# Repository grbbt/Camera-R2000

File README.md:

# R2000

> A compact, round-bodied digital camera built around the ESP32-P4, designed for fun, accessible photography with a deliberate film-inspired aesthetic.

---

## Overview

The R2000 is a hand-held digital camera on an 70mm circular PCB. Fixed-focus wide-angle lens, film-style filters, RGB flash, and a round touchscreen — all driven by an ESP32-P4 + ESP32-C6 SOM. It's a camera that prioritises feel and fun over clinical image quality.

---

## Features

- **80mm round PCB** — compact, pocketable form factor
- **OV5640 MIPI CSI-2 sensor** — 5MP, fixed focus, wide angle (~1.5m hyperfocal)
- **2.1" round ST7701S touchscreen** — live viewfinder and menu UI via LVGL
- **3-channel RGB flash** — independent R/G/B control for software-adjustable colour temperature
- **Film aesthetic filters** — colour grading, grain, vignette, and light leak applied in-camera
- **microSD card storage** — JPEG capture written directly from hardware encoder
- **USB-C** — charging and file transfer
- **1000mAh LiPo** — onboard single-cell battery

---

## Electrical Hardware

### Core SOM

**Guition JC-ESP32P4-M3-C6** — a dual-chip SOM combining:
- **ESP32-P4** — main application processor, MIPI CSI camera input, RGB display output, hardware JPEG encode, SD/MMC
- **ESP32-C6** — WiFi 6 / BLE 5 radio for wireless transfer and future remote control

### Schematic

### PCB

| Parameter | Value |
|-----------|-------|
| Diameter | 70mm |
| Layers | 4 |
| Design tool | KiCad |

- LDO bank placed adjacent to OV5640 to keep power traces short
- MT3608 boost converter isolated from camera rails to reduce switching noise
- RGB panel interface traces serpentined for length matching
- SD card traces kept short with 10kΩ pull-ups on CMD and DAT lines

### Camera

| Parameter | Value |
|-----------|-------|
| Sensor | OV5640 |
| Interface | MIPI CSI-2 (2-lane) |
| Resolution | 5MP (2592×1944) |
| Focus | Fixed, wide angle |
| Hyperfocal | ~1.5m (everything from ~80cm to ∞ sharp) |
| Autofocus | None — VCM unused |

### Display

| Parameter | Value |
|-----------|-------|
| Driver IC | ST7701S |
| Size | 2.1" round |
| Diameter | ~54mm |
| Interface | RGB parallel |
| Touch IC | GT911 (I2C) |

### Flash

Three independent channels let you tune the colour temperature of each shot in software — or go full auto white-balance assist by sampling the scene before firing.

| Channel | Driver | Supply |
|---------|--------|--------|
| Red 1W LED | AMC7135 (350mA CC) | 5V (MT3608 boost) |
| Green 1W LED | AMC7135 (350mA CC) | 5V (MT3608 boost) |
| Blue 1W LED | AMC7135 (350mA CC) | 5V (MT3608 boost) |

### Power

| Rail | Regulator | Supplies |
|------|-----------|---------|
| 3.3V | XC6210B332 (1A) | SOM, display logic, SD, GT911 |
| 2.8V | ME6211C28 (600mA) | OV5640 AVDD |
| 1.8V | ME6211C18 (600mA) | OV5640 DOVDD |
| 1.5V | ME6211C15 (600mA) | OV5640 DVDD |
| 5V (flash) | MT3608 boost | RGB flash rail |

Battery: 1000mAh single-cell LiPo, ~503040 form factor, charged via TP5100.

---

## Firmware

### Stack

| Layer | Component |
|-------|-----------|
| RTOS | FreeRTOS (via ESP-IDF v5.3+) |
| Camera | `esp_cam_sensor` + `esp_video` (MIPI CSI DMA) |
| JPEG encode | `esp_jpeg` — hardware-accelerated on ESP32-P4 |
| Display | `esp_lcd` (ST7701S) + `esp_lcd_touch` (GT911) |
| UI | LVGL — hardware-accelerated via P4 PPA |
| Storage | `esp_vfs_fat` + `sdmmc` |

### Task Architecture

```
Core 0                         Core 1
├── Camera capture task        ├── LVGL UI task
├── JPEG encode task           └── Touch polling task
└── SD write task
```

Both cores run in genuine parallel — the live viewfinder never stutters during a write.

### Capture Pipeline

```
OV5640 sensor
  └── MIPI CSI-2 DMA → PSRAM framebuffer
        └── HW JPEG encoder
              └── SD write (FAT32)
                    └── JPEG file
```

### Filters

- **Colour grading** — warm/cool/cross-process presets
- **Grain simulation** — luminance-dependent noise overlay
- **Vignette** — radial falloff, adjustable intensity
- **Light leak** — randomised edge flare, optional per-shot

---

## Getting Started

### Prerequisites

- ESP-IDF v5.3 or later ([installation guide](https://docs.espressif.com/projects/esp-idf/en/latest/esp32p4/get-started/))
- KiCad 8.x for hardware files

### Build Firmware

```bash
git clone https://github.com/yourusername/R2000.git
cd R2000/firmware

idf.py set-target esp32p4
idf.py menuconfig     # Set SD card GPIO, display config, etc.
idf.py build
idf.py -p /dev/ttyUSBx flash monitor
```

### Hardware Assembly

1. Order PCB from JLCPCB using files in `hardware/pcb/`
2. Source components from `hardware/bom/` — LCSC preferred for basic parts
3. Flash firmware before installing display and camera to simplify debug access

---

## GPIO Map

See [`docs/gpio_map.md`](docs/gpio_map.md) for the full 30-pin assignment covering RGB display, GT911 touch, OV5640 MIPI/I2C/XCLK, SD card, flash channels, and shutter button.

---

## Design Philosophy

The R2000 isn't trying to be a precise instrument. No AF hunting, no deep menus, no lab-grade colour science. Wide angle and fixed focus means everything is sharp the moment you raise it. The filters are baked in, not bolted on. Round is unusual and that's the point.

If you want clinical accuracy, this is the wrong camera. If you want something that makes you actually want to take pictures, that's what this is for.

---

## Status

| Electrical | Status |
|-----------|--------|
| PCB layout | ✅ First pass complete |
| Power system | ✅ LDO selection finalised |
| PCB Assembly & Testing | 🔧 In progress |

| Software | Status |
|-----------|--------|
| Display / LVGL | 🔧 In progress |
| WiFi upload (C6) | 🔧 In progress |
| RGB flash driver | ⬜ Not started |
| Film filters | ⬜ Not started |
| SD storage | ⬜ Not started |

| Hardware | Status |
|-----------|--------|
| Case Initial Design | 🔧 In progress |
| Case Prototyping | 🔧 In progress |

---

## License

Hardware and firmware released under [MIT License](LICENSE).

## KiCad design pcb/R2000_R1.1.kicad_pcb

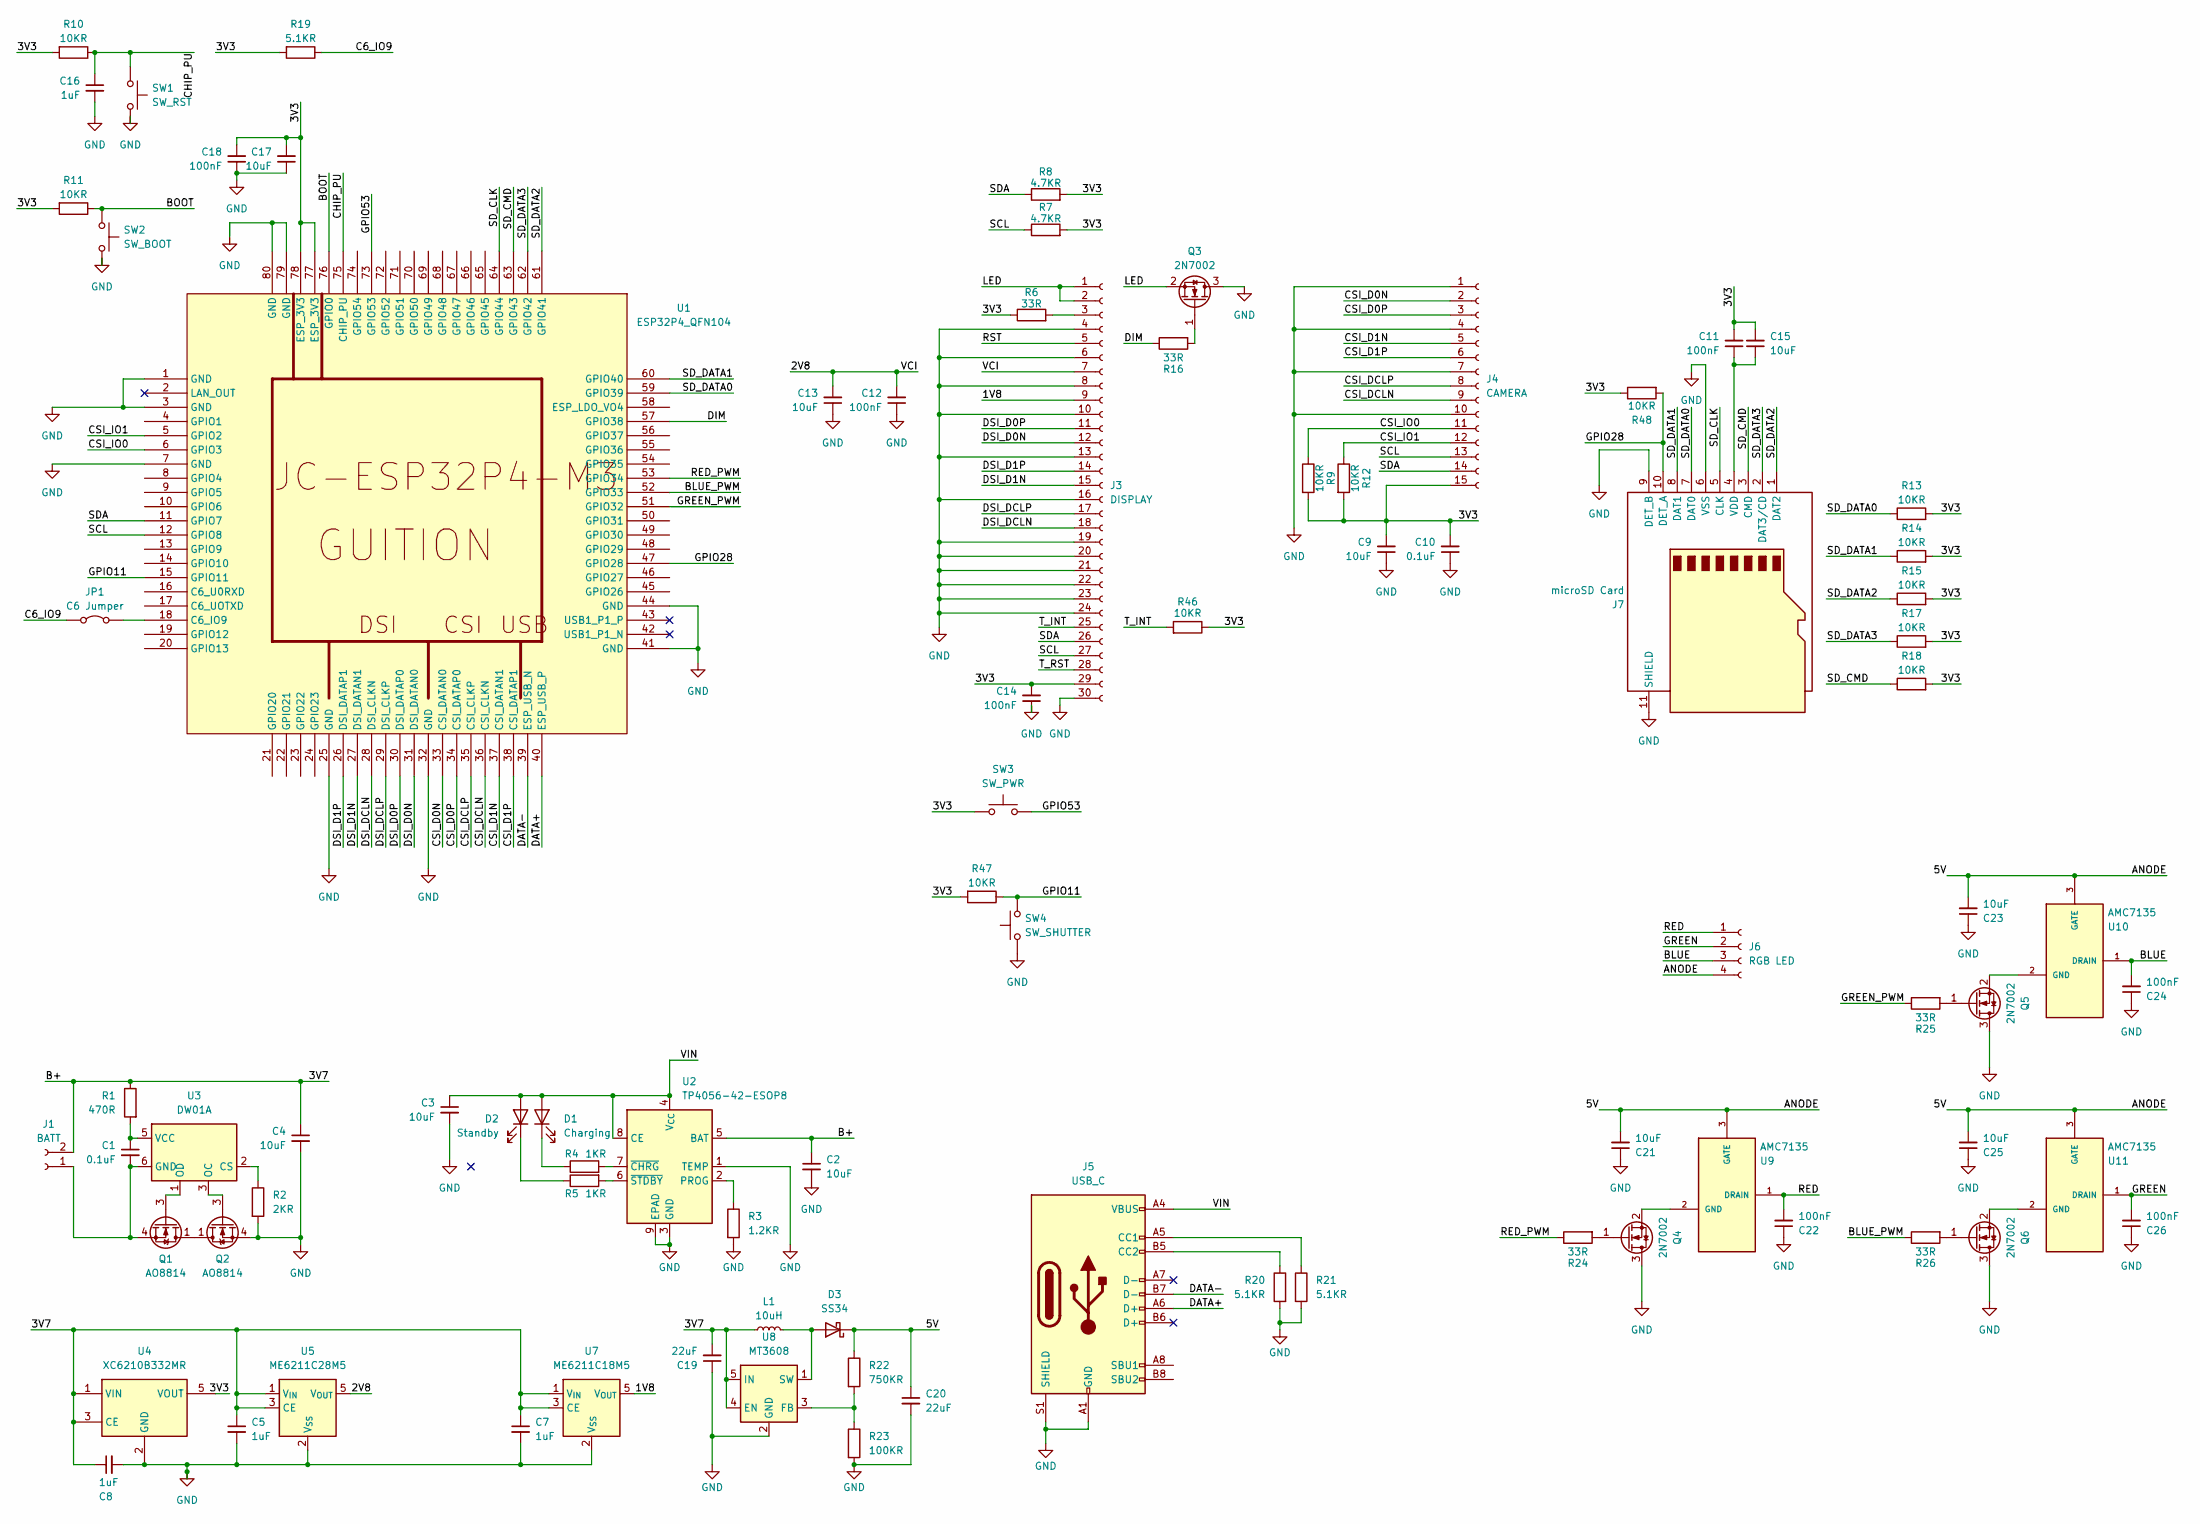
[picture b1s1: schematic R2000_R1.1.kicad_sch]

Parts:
C1, C10: 0.1uF; C_0805_2012Metric_Pad1.18x1.45mm_HandSolder
C2, C3, C4, C9, C13, C15, C17, C21, C23, C25: 10uF; C_0805_2012Metric_Pad1.18x1.45mm_HandSolder
C5, C7, C8, C16: 1uF; C_0805_2012Metric_Pad1.18x1.45mm_HandSolder
C11, C12, C14, C18, C22, C24, C26: 100nF; C_0805_2012Metric_Pad1.18x1.45mm_HandSolder
C19, C20: 22uF; C_0805_2012Metric_Pad1.18x1.45mm_HandSolder
D1: Charging; LED_1206_3216Metric_Pad1.42x1.75mm_HandSolder
D2: Standby; LED_1206_3216Metric_Pad1.42x1.75mm_HandSolder
D3: SS34; D_SMA
J1: BATT; JST_PH_B2B-PH-K_1x02_P2.00mm_Vertical
J3: DISPLAY; Hirose_FH12-30S-0.5SH_1x30-1MP_P0.50mm_Horizontal
J4: CAMERA; TE_1-84952-5_1x15-1MP_P1.0mm_Horizontal
J5: USB_C; USB_C_Receptacle_G-Switch_GT-USB-7010ASV
J6: RGB LED; PinHeader_1x04_P2.54mm_Vertical
J7: microSD Card; microSD_HC_Hirose_DM3AT-SF-PEJM5
JP1: C6 Jumper; PinHeader_1x02_P1.00mm_Vertical
L1: 10uH; L_Taiyo-Yuden_NR-60xx_HandSoldering
Q1, Q2: AO8814; TSOT-23-6
Q3, Q4, Q5, Q6: 2N7002; SOT-23
R1: 470R; R_0805_2012Metric_Pad1.20x1.40mm_HandSolder
R2: 2KR; R_0805_2012Metric_Pad1.20x1.40mm_HandSolder
R3: 1.2KR; R_0805_2012Metric_Pad1.20x1.40mm_HandSolder
R4, R5: 1KR; R_0805_2012Metric_Pad1.20x1.40mm_HandSolder
R6, R16, R24, R25, R26: 33R; R_0805_2012Metric_Pad1.20x1.40mm_HandSolder
R7, R8: 4.7KR; R_0805_2012Metric_Pad1.20x1.40mm_HandSolder
R9, R10, R11, R12, R13, R14, R15, R17, R18, R46, R47, R48: 10KR; R_0805_2012Metric_Pad1.20x1.40mm_HandSolder
R19, R20, R21: 5.1KR; R_0805_2012Metric_Pad1.20x1.40mm_HandSolder
R22: 750KR; R_0805_2012Metric_Pad1.20x1.40mm_HandSolder
R23: 100KR; R_0805_2012Metric_Pad1.20x1.40mm_HandSolder
SW1: SW_RST; SW_SPST_TL3342
SW2: SW_BOOT; SW_SPST_TL3342
SW3: SW_PWR; SW_Tactile_SPST_Angled_PTS645Vx58-2LFS
SW4: SW_SHUTTER; SW_Tactile_SPST_Angled_PTS645Vx58-2LFS
U1: ESP32P4_QFN104; JC-ESP32P4-M3_V0.2
U2: TP4056-42-ESOP8; SOIC-8-1EP_3.9x4.9mm_P1.27mm_EP2.41x3.3mm_ThermalVias
U3: DW01A; SOT-23-6
U4: XC6210B332MR; SOT-23-5
U5: ME6211C28M5; SOT-23-5
U7: ME6211C18M5; SOT-23-5
U8: MT3608; SOT-23-6
U9, U10, U11: AMC7135; AMC7135_ASAP

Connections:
/1V8: J3.9, U7.5 (V_{OUT})
/2V8: C12.2, C13.2, J3.7, U5.5 (V_{OUT})
/3V3: C9.2, C10.2, C11.2, C14.2, C15.2, C17.2, C18.2, J3.29, J4.15, R6.1, R7.2, R8.2, R9.2, R10.2, R11.2, R12.2, R13.2, R14.2, R15.2, R17.2, R18.2, R19.2, R46.1, R47.2, R48.1, SW3.1, U1.77 (ESP_3V3), U1.78 (ESP_3V3), U4.5 (VOUT); also elsewhere on the board
/3V7: C2.1, C4.1, C5.1, C7.1, C8.1, C19.2, J1.2, L1.1, R1.1, U2.5 (BAT), U4.1 (VIN), U4.3 (CE), U5.1 (V_{IN}), U5.3 (CE), U7.1 (V_{IN}), U7.3 (CE), U8.4 (EN), U8.5 (IN); also elsewhere on the board
/5V: C20.1, C21.2, C23.2, C25.2, D3.1 (K), J6.4, R22.1, U9.3 (GATE), U10.3 (GATE), U11.3 (GATE)
/BLUE: C24.2, J6.3, U10.1 (DRAIN)
/BLUE_PWM: R26.1, U1.52 (GPIO33)
/BOOT: R11.1, SW2.1, U1.76 (GPIO0)
/C6_IO9: JP1.1 (A), R19.1
/CHIP_PU: C16.1, R10.1, SW1.1, U1.75 (CHIP_PU)
/CSI_D0N: J4.2, U1.33 (CSI_DATAN0)
/CSI_D0P: J4.3, U1.34 (CSI_DATAP0)
/CSI_D1N: J4.5, U1.37 (CSI_DATAN1)
/CSI_D1P: J4.6, U1.38 (CSI_DATAP1)
/CSI_DCLN: J4.9, U1.36 (CSI_CLKN)
/CSI_DCLP: J4.8, U1.35 (CSI_CLKP)
/CSI_IO0: J4.11, R9.1, U1.6 (GPIO3)
/CSI_IO1: J4.12, R12.1, U1.5 (GPIO2)
/DATA+: J5.A6 (D+), U1.40 (ESP_USB_P)
/DATA-: J5.B7 (D-), U1.39 (ESP_USB_N)
/DIM: R16.1, U1.57 (GPIO38)
/DSI_D0N: J3.12, U1.31 (DSI_DATAN0)
/DSI_D0P: J3.11, U1.30 (DSI_DATAP0)
/DSI_D1N: J3.15, U1.27 (DSI_DATAN1)
/DSI_D1P: J3.14, U1.26 (DSI_DATAP1)
/DSI_DCLN: J3.18, U1.28 (DSI_CLKN)
/DSI_DCLP: J3.17, U1.29 (DSI_CLKP)
/GPIO11: R47.1, SW4.2, U1.15 (GPIO11); also elsewhere on the board
/GPIO28: J7.10 (DET_A), R48.2, U1.47 (GPIO28)
/GPIO53: SW3.2, U1.73 (GPIO53); also elsewhere on the board
/GREEN: C26.2, J6.2, U11.1 (DRAIN)
/GREEN_PWM: R25.1, U1.51 (GPIO32)
/LED: J3.1, J3.2, Q3.2 (S)
/RED: C22.2, J6.1, U9.1 (DRAIN)
/RED_PWM: R24.1, U1.53 (GPIO34)
/RST: J3.5
/SCL: J3.27, J4.13, R7.1, U1.12 (GPIO8)
/SDA: J3.26, J4.14, R8.1, U1.11 (GPIO7)
/SD_CLK: J7.5 (CLK), U1.64 (GPIO44)
/SD_CMD: J7.3 (CMD), R18.1, U1.63 (GPIO43)
/SD_DATA0: J7.7 (DAT0), R13.1, U1.59 (GPIO39)
/SD_DATA1: J7.8 (DAT1), R14.1, U1.60 (GPIO40)
/SD_DATA2: J7.1 (DAT2), R15.1, U1.61 (GPIO41)
/SD_DATA3: J7.2 (DAT3/CD), R17.1, U1.62 (GPIO42)
/T_INT: J3.25, R46.2
/T_RST: J3.28
/VIN: C3.1, D1.2 (A), D2.2 (A), J5.A4 (VBUS), J5.A9 (VBUS), J5.B4 (VBUS), J5.B9 (VBUS), U2.4 (V_{CC}), U2.8 (CE)
GND: C2.2, C3.2, C4.2, C5.2, C7.2, C8.2, C9.1, C10.1, C12.1, C13.1, C14.1, C16.2, C17.1, C18.1, C19.1, C20.2, C21.1, C22.1, C23.1, C24.1, C25.1, C26.1, J3.4, J3.6, J3.8, J3.10, J3.13, J3.16, J3.19, J3.20, J3.21, J3.22, J3.23, J3.24, J3.30, J4.1, J4.4, J4.7, J4.10, J5.A1 (GND), J5.A12 (GND), J5.B1 (GND), J5.B12 (GND), J5.S1 (SHIELD), J7.6 (VSS), J7.9 (DET_B), J7.11 (SHIELD), Q2.4 (S), Q3.3 (D), Q4.3 (D), Q5.3 (D), Q6.3 (D), R2.2, R3.2, R20.2, R21.2, R23.2, SW1.2, SW2.2, SW4.1, U1.1 (GND), U1.3 (GND), U1.7 (GND), U1.25 (GND), U1.32 (GND), U1.41 (GND), U1.44 (GND), U1.79 (GND), U1.80 (GND), U2.1 (TEMP), U2.3 (GND), U2.9 (EPAD), U4.2 (GND), U5.2 (V_{SS}), U7.2 (V_{SS}), U8.2 (GND); also elsewhere on the board
unnamed: D1.1 (K), R4.1
unnamed: D2.1 (K), R5.1
unnamed 50: D3.2 (A), L1.2, U8.1 (SW); also elsewhere on the board
unnamed: C1.2, J1.1, Q1.4 (S), U3.6 (GND)
unnamed: J3.3, R6.2
unnamed: J5.A5 (CC1), R21.1
unnamed: J5.B5 (CC2), R20.1
unnamed: C11.1, C15.1, J7.4 (VDD)
unnamed: JP1.2 (B), U1.18 (C6_IO9)
unnamed: Q1.1 (D), Q1.2 (D), Q1.5 (D), Q1.6 (D), Q2.1 (D), Q2.2 (D), Q2.5 (D), Q2.6 (D)
unnamed: Q1.3 (G), U3.1 (OD)
unnamed: Q2.3 (G), U3.3 (OC)
unnamed: Q3.1 (G), R16.2
unnamed: Q4.1 (G), R24.2
unnamed: Q4.2 (S), U9.2 (GND), U9.2@1 (GND)
unnamed: Q5.1 (G), R25.2
unnamed: Q5.2 (S), U10.2 (GND), U10.2@1 (GND)
unnamed: Q6.1 (G), R26.2
unnamed: Q6.2 (S), U11.2 (GND), U11.2@1 (GND)
unnamed: R3.1, U2.2 (PROG)
unnamed: R4.2, U2.7 (~CHRG)
unnamed: R5.2, U2.6 (~STDBY)
unnamed: R2.1, U3.2 (CS)
unnamed: C1.1, R1.2, U3.5 (VCC)
unnamed 72: R22.2, R23.1, U8.3 (FB); also elsewhere on the board

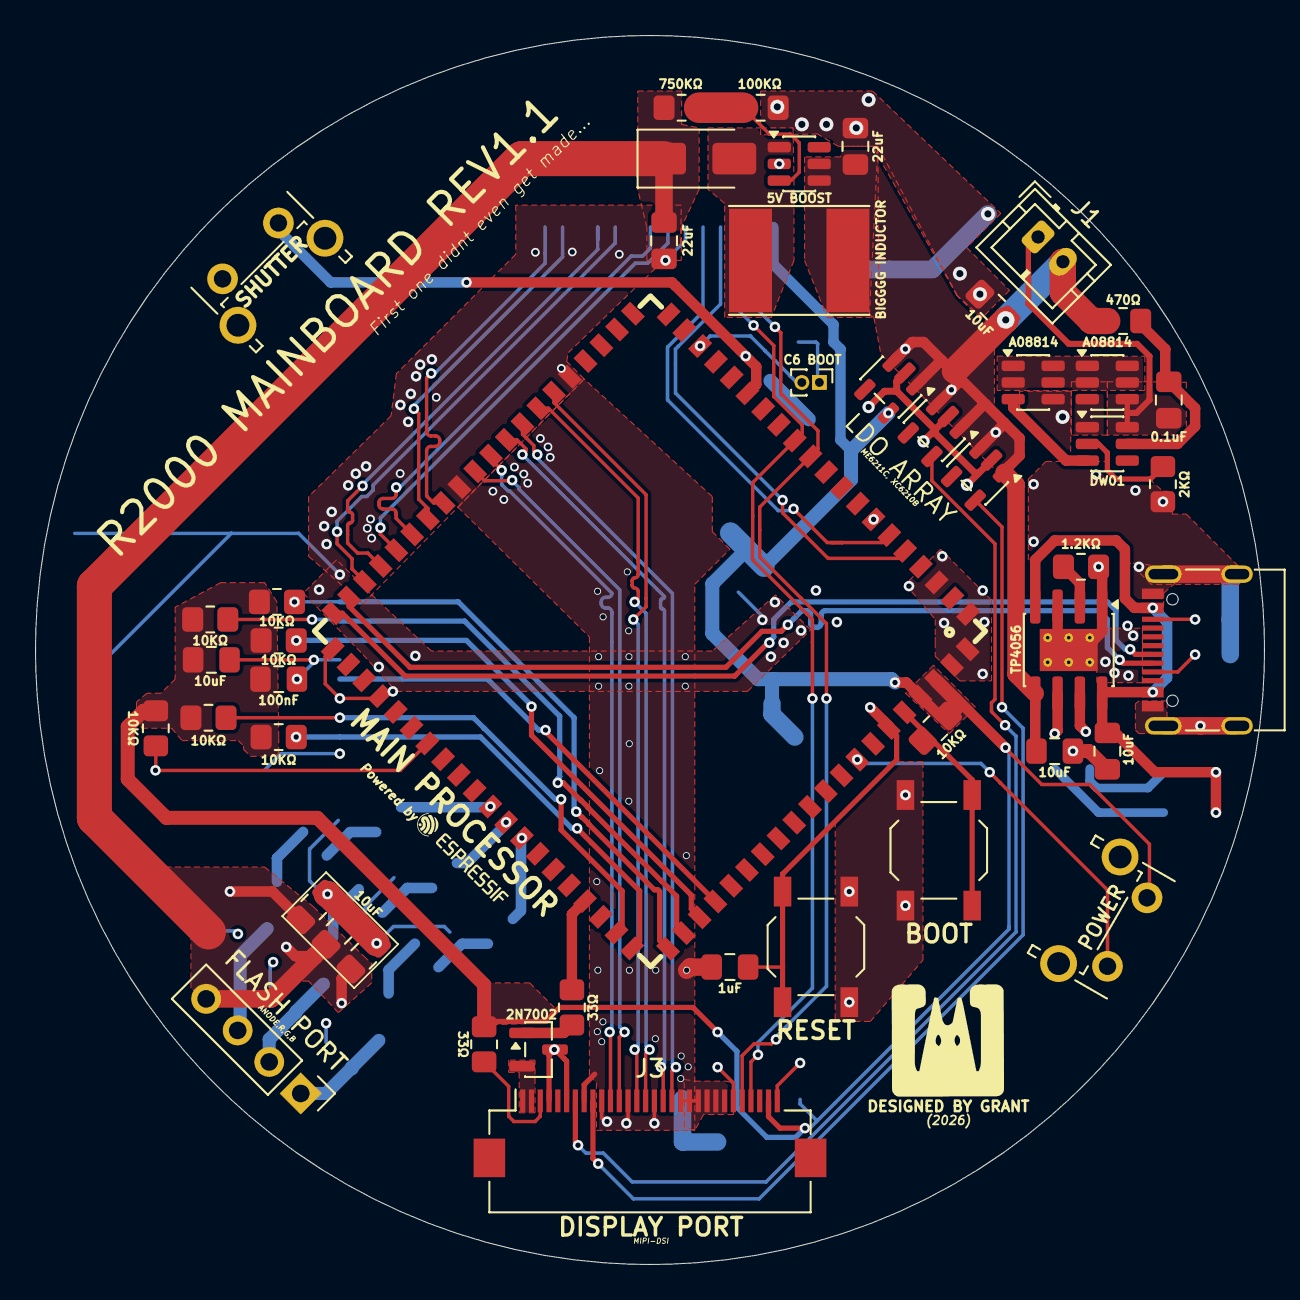
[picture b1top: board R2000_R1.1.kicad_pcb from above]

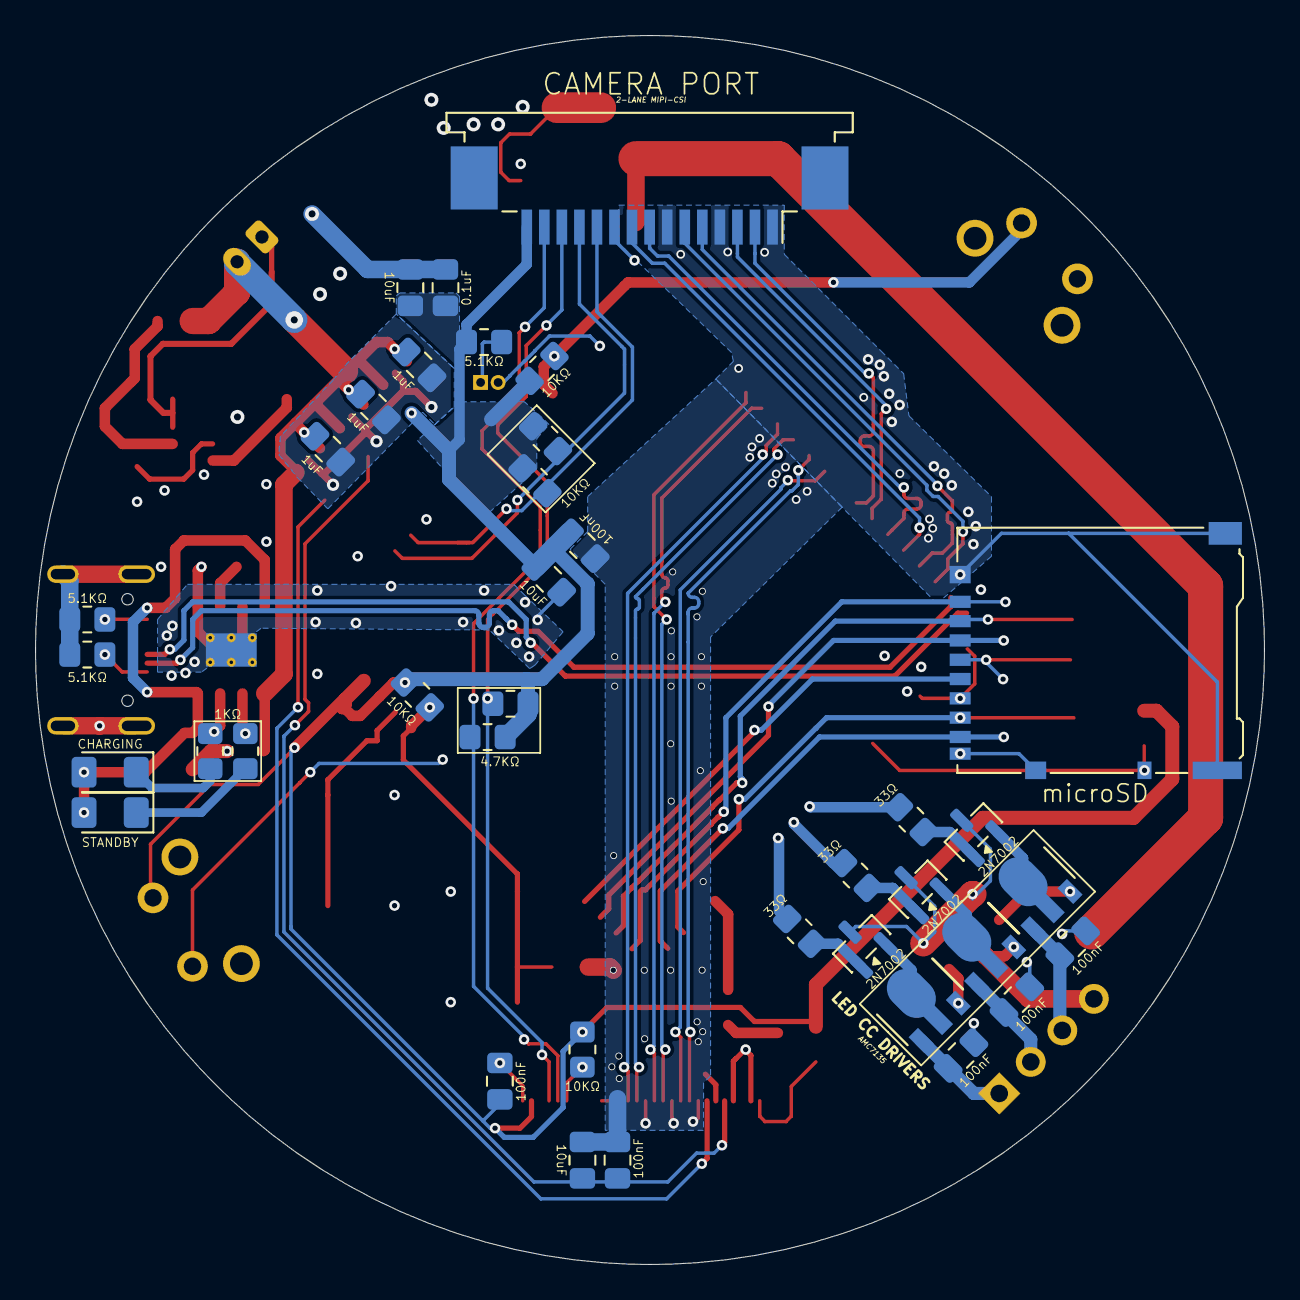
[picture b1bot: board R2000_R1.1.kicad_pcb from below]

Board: 4 copper layers, 70.0 x 70.0 mm, 85 parts (38 on the bottom side), 71 nets.

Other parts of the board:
5V BOOST: MT3608; SOT-23-6
BIGGGG INDUCTOR: 10uH; L_Taiyo-Yuden_NR-60xx_HandSoldering
POWER: SW_PWR; SW_Tactile_SPST_Angled_PTS645Vx58-2LFS
SHUTTER: SW_SHUTTER; SW_Tactile_SPST_Angled_PTS645Vx58-2LFS

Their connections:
/3V3: POWER.1; also elsewhere on the board
/3V7: 5V BOOST.4 (EN), 5V BOOST.5 (IN), BIGGGG INDUCTOR.1; also elsewhere on the board
/GPIO11: SHUTTER.2; also elsewhere on the board
/GPIO53: POWER.2; also elsewhere on the board
GND: 5V BOOST.2 (GND), SHUTTER.1; also elsewhere on the board
unnamed 50: 5V BOOST.1 (SW), BIGGGG INDUCTOR.2; also elsewhere on the board
unnamed 72: 5V BOOST.3 (FB); also elsewhere on the board

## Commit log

2026-05-20 Rename image.png to schematic.png
2026-05-20 Update LICENSE
